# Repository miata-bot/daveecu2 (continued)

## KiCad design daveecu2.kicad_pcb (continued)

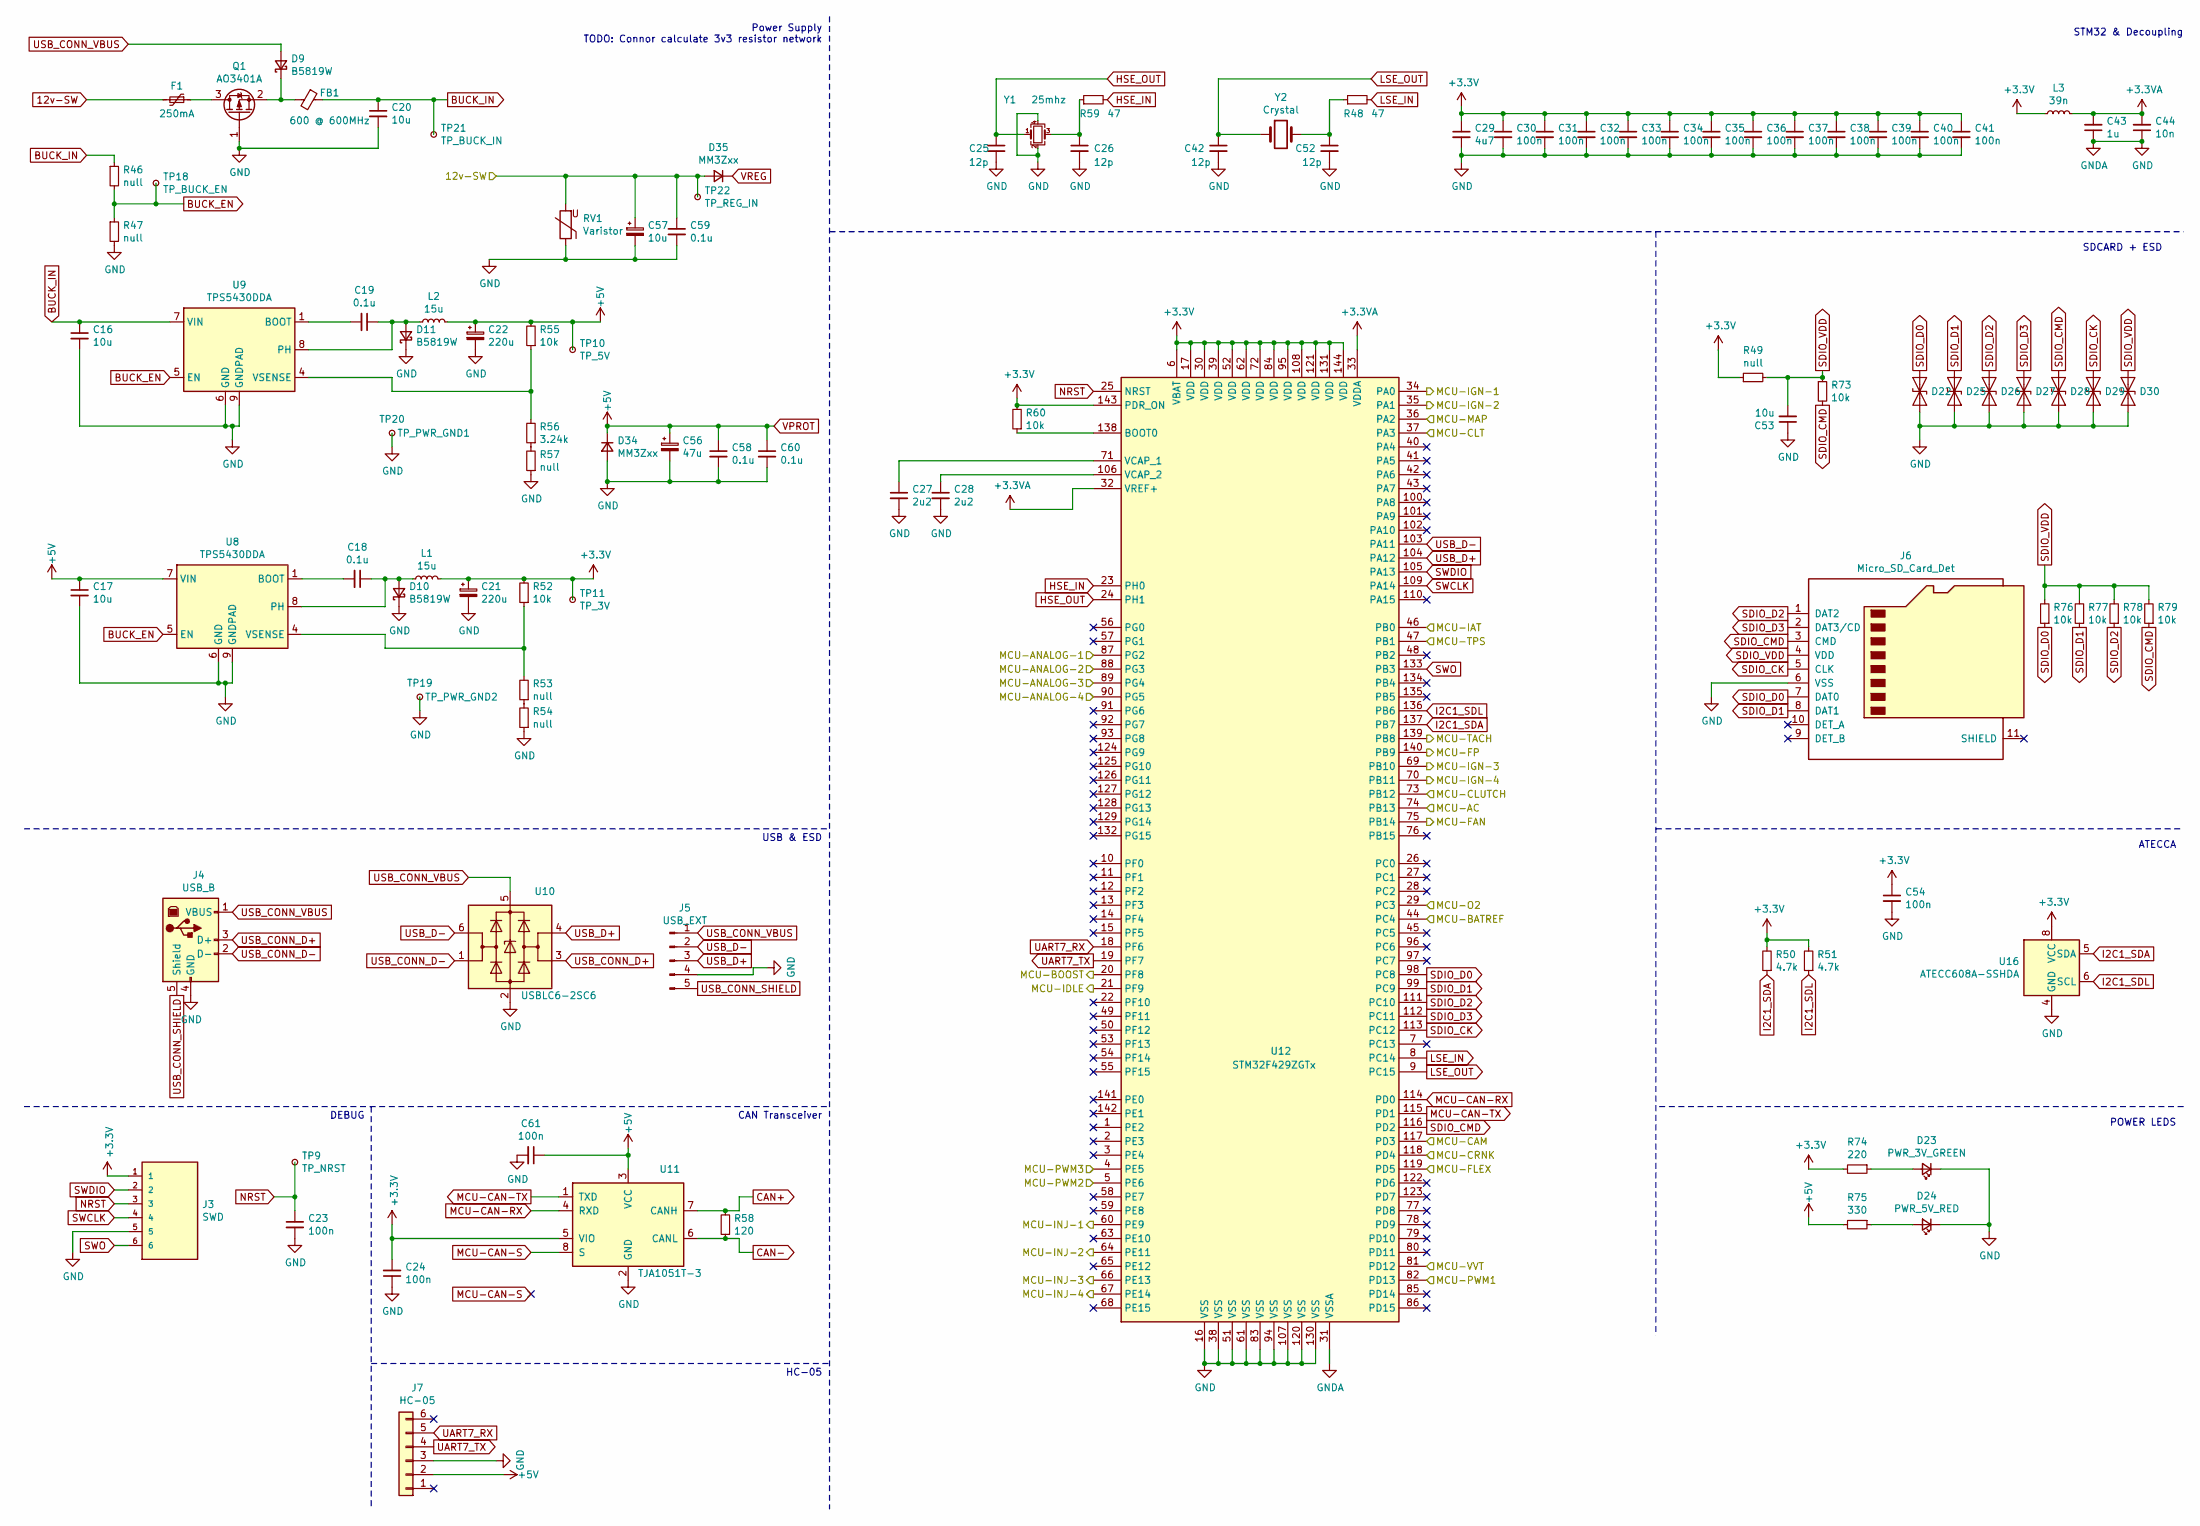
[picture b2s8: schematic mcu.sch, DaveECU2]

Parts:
C16, C17: 10u; C_1206_3216Metric_Pad1.33x1.80mm_HandSolder
C18, C19: 0.1u; C_0603_1608Metric_Pad1.08x0.95mm_HandSolder
C20: 10u; C_0603_1608Metric_Pad1.08x0.95mm_HandSolder
C21, C22: 220u; CP_Elec_10x14.3; LCSC_PN C401904
C23, C24, C30, C31, C32, C33, C34, C35, C36, C37, C38, C39, C40, C41, C54, C61: 100n; C_0402_1005Metric_Pad0.74x0.62mm_HandSolder
C25, C26, C42, C52: 12p; C_0402_1005Metric_Pad0.74x0.62mm_HandSolder
C27, C28: 2u2; C_0603_1608Metric_Pad1.08x0.95mm_HandSolder
C29: 4u7; C_0603_1608Metric_Pad1.08x0.95mm_HandSolder
C43: 1u; C_0402_1005Metric_Pad0.74x0.62mm_HandSolder
C44: 10n; C_0402_1005Metric_Pad0.74x0.62mm_HandSolder
C53: 10u; C_0402_1005Metric_Pad0.74x0.62mm_HandSolder
C56: 47u; CP_Elec_5x5.8; LCSC_PN C336380
C57: 10u; CP_EIA-7343-20_Kemet-V_Pad2.25x2.55mm_HandSolder; LCSC_PN C117038
C58, C59, C60: 0.1u; C_1206_3216Metric_Pad1.33x1.80mm_HandSolder; LCSC_PN C141184
D9, D10, D11: B5819W; D_SOD-123; LCSC_PN C541627
D22, D25, D26, D27, D28, D29, D30: ESD9B3.3ST5G; D_SOD-923; LCSC_PN C96512
D23: PWR_3V_GREEN; LED_0603_1608Metric_Pad1.05x0.95mm_HandSolder; LCSC_PN C440518
D24: PWR_5V_RED; LED_0603_1608Metric_Pad1.05x0.95mm_HandSolder; LCSC_PN C192315
D34, D35: MM3Zxx; D_SOD-323_HandSoldering; LCSC_PN C152524
F1: 250mA; Fuse_1206_3216Metric_Pad1.42x1.75mm_HandSolder
FB1: 600 @ 600MHz; L_0805_2012Metric_Pad1.05x1.20mm_HandSolder
J3: SWD; TAG_TC2030-IDC-NL; PARTREV MS
J4: USB_B; USB_B_Lumberg_2411_02_Horizontal
J5: USB_EXT; PinHeader_1x05_P2.54mm_Vertical_SMD_Pin1Left
J6: Micro_SD_Card_Det; microSD_HC_Molex_104031-0811
J7: HC-05; PinHeader_1x06_P2.54mm_Vertical
L1, L2: 15u; L_Sunlord_MWSA0518_5.4x5.2mm; LCSC_PN C139506
L3: 39n; L_0402_1005Metric_Pad0.77x0.64mm_HandSolder
Q1: AO3401A; SOT-23
R46, R47, R49, R53, R54, R57: null; R_0603_1608Metric_Pad0.98x0.95mm_HandSolder
R48, R59: 47; R_0402_1005Metric_Pad0.72x0.64mm_HandSolder
R50, R51: 4.7k; R_0603_1608Metric_Pad0.98x0.95mm_HandSolder
R52, R55, R73, R76, R77, R78, R79: 10k; R_0603_1608Metric_Pad0.98x0.95mm_HandSolder
R56: 3.24k; R_0603_1608Metric_Pad0.98x0.95mm_HandSolder
R58: 120; R_0603_1608Metric_Pad0.98x0.95mm_HandSolder
R60: 10k; R_0402_1005Metric_Pad0.72x0.64mm_HandSolder
R74: 220; R_0603_1608Metric_Pad0.98x0.95mm_HandSolder
R75: 330; R_0603_1608Metric_Pad0.98x0.95mm_HandSolder
RV1: Varistor; RV_Disc_D15.5mm_W3.9mm_P7.5mm; LCSC_PN C1527916
TP9: TP_NRST; TestPoint_Pad_D1.0mm
TP10: TP_5V; TestPoint_Pad_D1.0mm
TP11: TP_3V; TestPoint_Pad_D1.0mm
TP18: TP_BUCK_EN; TestPoint_Pad_D1.0mm
TP19: TP_PWR_GND2; TestPoint_Pad_D1.0mm
TP20: TP_PWR_GND1; TestPoint_Pad_D1.0mm
TP21: TP_BUCK_IN; TestPoint_Pad_D1.0mm
TP22: TP_REG_IN; TestPoint_Pad_D1.0mm
U8, U9: TPS5430DDA; TI_SO-PowerPAD-8_ThermalVias
U10: USBLC6-2SC6; SOT-23-6
U11: TJA1051T-3; SOIC-8_3.9x4.9mm_P1.27mm
U12: STM32F429ZGTx; LQFP-144_20x20mm_P0.5mm
U16: ATECC608A-SSHDA; SOIC-8_3.9x4.9mm_P1.27mm; LCSC_PN C2650407
Y1: 25mhz; Crystal_SMD_3225-4Pin_3.2x2.5mm_HandSoldering; LCSC_PN C439049
Y2: Crystal; Crystal_SMD_3215-2Pin_3.2x1.5mm; LCSC_PN C97604

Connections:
12v-SW: C57.1, C59.1, D35.2 (A), F1.2, RV1.2, TP22.1; also elsewhere on the board
+3.3VA: C43.2, C44.2, L3.2, U12.32 (VREF+), U12.33 (VDDA)
+3V3: C21.1, C24.2, C29.1, C30.1, C31.1, C32.1, C33.1, C34.1, C35.1, C36.1, C37.1, C38.1, C39.1, C40.1, C41.1, C54.1, J3.1, L1.2, L3.1, R49.1, R50.2, R51.2, R52.2, R60.2, R74.2, TP11.1, U11.5 (VIO), U12.6 (VBAT), U12.17 (VDD), U12.30 (VDD), U12.39 (VDD), U12.52 (VDD), U12.62 (VDD), U12.72 (VDD), U12.84 (VDD), U12.95 (VDD), U12.108 (VDD), U12.121 (VDD), U12.131 (VDD), U12.143 (PDR_ON), U12.144 (VDD), U16.8 (VCC)
/FAN+TACH/MCU-FAN: U12.75 (PB14); also elsewhere on the board
/FAN+TACH/MCU-FP: U12.140 (PB9); also elsewhere on the board
/FAN+TACH/MCU-TACH: U12.139 (PB8); also elsewhere on the board
/IDLE+BOOST/MCU-BOOST: U12.20 (PF8); also elsewhere on the board
/IDLE+BOOST/MCU-IDLE: U12.21 (PF9); also elsewhere on the board
/Ignitors/MCU-IGN-1: U12.34 (PA0); also elsewhere on the board
/Ignitors/MCU-IGN-2: U12.35 (PA1); also elsewhere on the board
/Ignitors/MCU-IGN-3: U12.69 (PB10); also elsewhere on the board
/Ignitors/MCU-IGN-4: U12.70 (PB11); also elsewhere on the board
/Injectors/MCU-INJ-1: U12.60 (PE9); also elsewhere on the board
/Injectors/MCU-INJ-2: U12.64 (PE11); also elsewhere on the board
/Injectors/MCU-INJ-3: U12.66 (PE13); also elsewhere on the board
/Injectors/MCU-INJ-4: U12.67 (PE14); also elsewhere on the board
/Sensors/MCU-AC: U12.74 (PB13); also elsewhere on the board
/Sensors/MCU-CLUTCH: U12.73 (PB12); also elsewhere on the board
/mcu/MCU-PWM1: U12.82 (PD13); also elsewhere on the board
/mcu/MCU-PWM2: U12.5 (PE6); also elsewhere on the board
/mcu/MCU-PWM3: U12.4 (PE5); also elsewhere on the board
/mcu/MCU-VVT: U12.81 (PD12); also elsewhere on the board
ADC-CLAMP-1: U12.87 (PG2); also elsewhere on the board
ADC-CLAMP-2: U12.88 (PG3); also elsewhere on the board
ADC-CLAMP-3: U12.89 (PG4); also elsewhere on the board
ADC-CLAMP-4: U12.90 (PG5); also elsewhere on the board
ADC-CLAMP-5: U12.118 (PD4); also elsewhere on the board
ADC-CLAMP-6: U12.117 (PD3); also elsewhere on the board
ADC-CLAMP-7: U12.119 (PD5); also elsewhere on the board
ADC-CLAMP-9: U12.36 (PA2); also elsewhere on the board
ADC-CLAMP-10: U12.37 (PA3); also elsewhere on the board
ADC-CLAMP-11: U12.29 (PC3); also elsewhere on the board
ADC-CLAMP-12: U12.44 (PC4); also elsewhere on the board
ADC-CLAMP-13: U12.46 (PB0); also elsewhere on the board
ADC-CLAMP-14: U12.47 (PB1); also elsewhere on the board
BUCK_EN: R46.2, R47.1, TP18.1, U8.5 (EN), U9.5 (EN)
BUCK_IN: C16.1, C20.1, FB1.1, R46.1, TP21.1, U9.7 (VIN)
CAN+: R58.2, U11.7 (CANH); also elsewhere on the board
CAN-: R58.1, U11.6 (CANL); also elsewhere on the board
GND: C16.2, C17.2, C20.2, C21.2, C22.2, C23.2, C24.1, C25.2, C26.2, C27.2, C28.2, C29.2, C30.2, C31.2, C32.2, C33.2, C34.2, C35.2, C36.2, C37.2, C38.2, C39.2, C40.2, C41.2, C42.2, C43.1, C44.1, C52.2, C53.1, C54.2, C56.2, C57.2, C58.2, C59.2, C60.2, C61.2, D10.1 (K), D11.1 (K), D22.2 (A2), D23.1 (K), D24.1 (K), D25.2 (A2), D26.2 (A2), D27.2 (A2), D28.2 (A2), D29.2 (A2), D30.2 (A2), D34.2 (A), J3.5, J4.4 (GND), J5.4, J6.6 (VSS), J7.3, Q1.1 (G), R47.2, R54.1, R57.1, RV1.1, TP19.1, TP20.1, U8.6 (GND), U8.9 (GNDPAD), U9.6 (GND), U9.9 (GNDPAD), U10.2 (GND), U11.2 (GND), U12.16 (VSS), U12.31 (VSSA), U12.38 (VSS), U12.51 (VSS), U12.61 (VSS), U12.83 (VSS), U12.94 (VSS), U12.107 (VSS), U12.120 (VSS), U12.130 (VSS), U16.4 (GND), Y1.2, Y1.4; also elsewhere on the board
HSE_IN: R59.2, U12.23 (PH0)
HSE_OUT: C25.1, U12.24 (PH1), Y1.1
I2C1_SDA: R50.1, U12.137 (PB7), U16.5 (SDA)
I2C1_SDL: R51.1, U12.136 (PB6), U16.6 (SCL)
LSE_IN: R48.2, U12.8 (PC14)
LSE_OUT: C42.1, U12.9 (PC15), Y2.1
MCU-CAN-RX: U11.4 (RXD), U12.114 (PD0)
MCU-CAN-TX: U11.1 (TXD), U12.115 (PD1)
NRST: C23.1, J3.3, TP9.1, U12.25 (NRST)
unnamed: C18.1, D10.2 (A), L1.1, U8.8 (PH)
unnamed: C18.2, U8.1 (BOOT)
unnamed: C19.1, D11.2 (A), L2.1, U9.8 (PH)
unnamed: C19.2, U9.1 (BOOT)
unnamed: C26.1, R59.1, Y1.3
unnamed: C27.1, U12.71 (VCAP_1)
unnamed: C28.1, U12.106 (VCAP_2)
unnamed: C52.1, R48.1, Y2.2
unnamed: D9.1 (K), FB1.2, Q1.2 (S)
unnamed: D23.2 (A), R74.1
unnamed: D24.2 (A), R75.1
unnamed: F1.1, Q1.3 (D)
unnamed: R52.1, R53.2, U8.4 (VSENSE)
unnamed: R53.1, R54.2
unnamed: R55.1, R56.2, U9.4 (VSENSE)
unnamed: R56.1, R57.2
unnamed: R60.1, U12.138 (BOOT0)
SDIO_CK: D29.1 (A1), J6.5 (CLK), U12.113 (PC12)
SDIO_CMD: D28.1 (A1), J6.3 (CMD), R73.2, R79.1, U12.116 (PD2)
SDIO_D0: D22.1 (A1), J6.7 (DAT0), R76.1, U12.98 (PC8)
SDIO_D1: D25.1 (A1), J6.8 (DAT1), R77.1, U12.99 (PC9)
SDIO_D2: D26.1 (A1), J6.1 (DAT2), R78.1, U12.111 (PC10)
SDIO_D3: D27.1 (A1), J6.2 (DAT3/CD), U12.112 (PC11)
SDIO_VDD: C53.2, D30.1 (A1), J6.4 (VDD), R49.2, R73.1, R76.2, R77.2, R78.2, R79.2
SWCLK: J3.4, U12.109 (PA14)
SWDIO: J3.2, U12.105 (PA13)
SWO: J3.6, U12.133 (PB3)
UART7_RX: J7.5, U12.18 (PF6)
UART7_TX: J7.4, U12.19 (PF7)
USB_CONN_D+: J4.3 (D+), U10.3 (I/O2)
USB_CONN_D-: J4.2 (D-), U10.1 (I/O1)
USB_CONN_SHIELD: J4.5 (Shield), J5.5
USB_CONN_VBUS: D9.2 (A), J4.1 (VBUS), J5.1, U10.5 (VBUS)
USB_D+: J5.3, U10.4 (I/O2), U12.104 (PA12)
USB_D-: J5.2, U10.6 (I/O1), U12.103 (PA11)
VPROT: C17.1, C22.1, C56.1, C58.1, C60.1, C61.1, D34.1 (K), J7.2, L2.2, R55.2, R75.2, TP10.1, U8.7 (VIN), U11.3 (VCC); also elsewhere on the board
VREG: D35.1 (K); also elsewhere on the board

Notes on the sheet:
Power Supply TODO: Connor calculate 3v3 resistor network
USB & ESD
DEBUG
STM32 & Decoupling
CAN Transceiver
SDCARD + ESD
ATECCA
POWER LEDS
HC-05

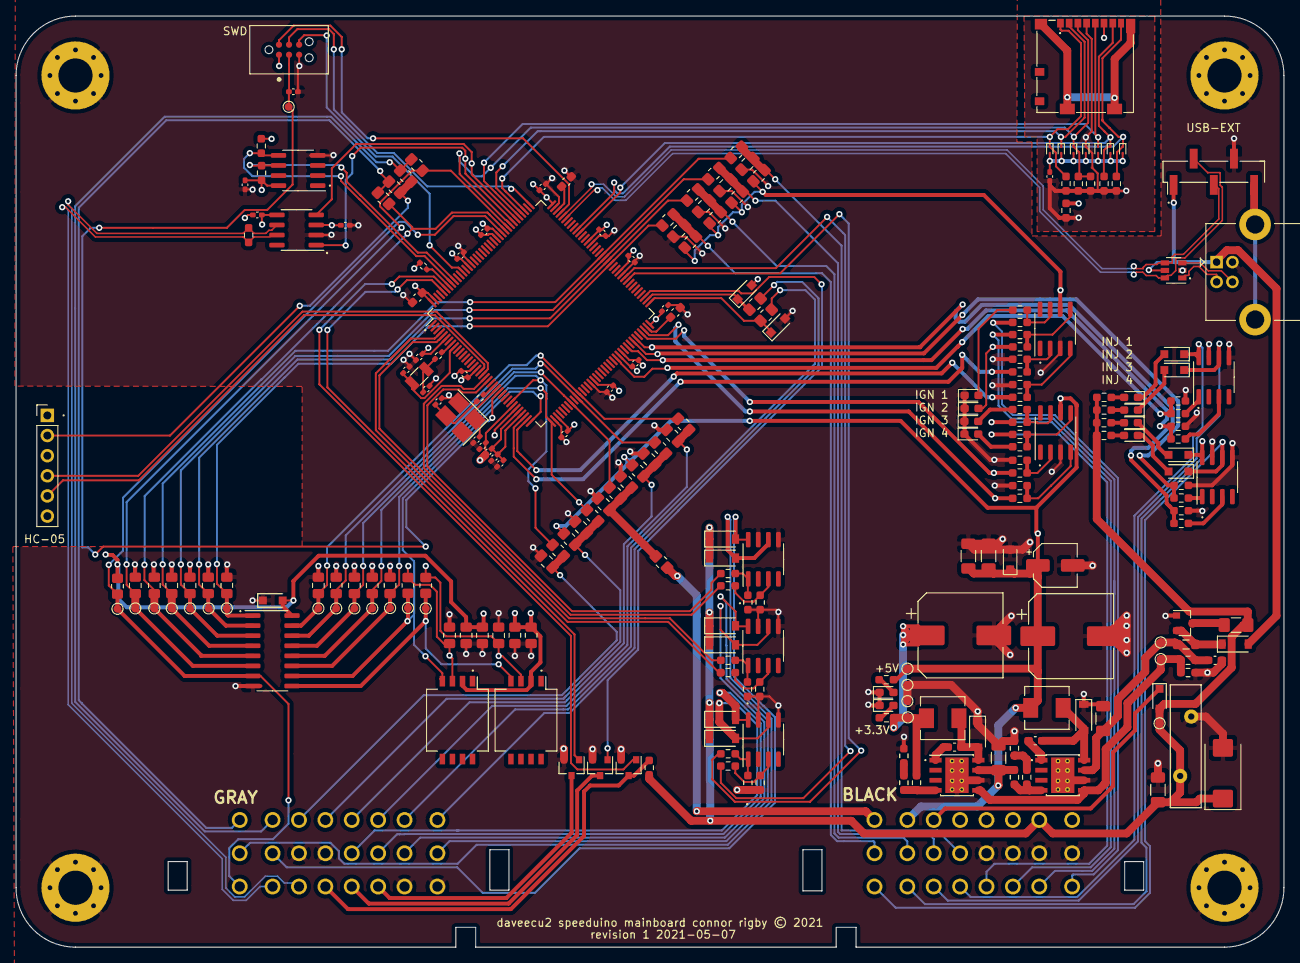
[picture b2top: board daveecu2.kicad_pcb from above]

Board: 4 copper layers, 160.0 x 117.5 mm, 249 parts (0 on the bottom side), 150 nets.

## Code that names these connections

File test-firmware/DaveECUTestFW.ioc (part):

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PB13.GPIOParameters=GPIO_Label
PD12.GPIO_Label=VVT
PE11.GPIOParameters=GPIO_Label
PG4.Signal=GPIO_Analog
PC12.Signal=SDIO_CK
PB14.GPIO_Label=FAN
PD3.GPIOParameters=GPIO_Label
PA3.GPIOParameters=GPIO_Label
PB13.Signal=GPIO_Input
PA2.GPIOParameters=GPIO_Label
RCC.SYSCLKSource=RCC_SYSCLKSOURCE_HSE
PA4.Mode=NSS_Signal_Hard_Input
PF7.Signal=UART7_TX
PD4.Signal=GPXTI4
PB6.Signal=I2C1_SCL
PH1/OSC_OUT.Signal=RCC_OSC_OUT
PB6.Mode=I2C
PC3.Signal=GPIO_Analog
PD0.Signal=CAN1_RX
PE5.Signal=S_TIM9_CH1
PB3.Mode=Trace_Asynchronous_SW
PB12.GPIO_Label=LAUNCH
PB0.GPIOParameters=GPIO_Label
PA1.GPIOParameters=GPIO_Label
PC4.GPIO_Label=BAT
PE9.Signal=S_TIM1_CH1
PB1.GPIO_Label=TPS
PC9.Mode=SD_4_bits_Wide_bus
PA8.Signal=GPIO_Output
PB14.Stacked=true
Mcu.Package=LQFP144
PB9.Signal=S_TIM4_CH4
PB1.Signal=ADCx_IN9
PF8.GPIOParameters=GPIO_Label
PD12.Signal=S_TIM4_CH1
PD5.GPIOParameters=GPIO_Label
PA10.Signal=GPIO_Output
PC11.Mode=SD_4_bits_Wide_bus
PB14.GPIOParameters=GPIO_Label
PB10.GPIOParameters=GPIO_Label
PC4.GPIOParameters=GPIO_Label
PA5.Mode=Full_Duplex_Master
PA0/WKUP.GPIOParameters=GPIO_Label
PG5.Signal=GPIO_Analog
PA9.GPIO_Label=RN1
PD3.Signal=GPXTI3
PB11.GPIO_Label=IGN4
PD1.Signal=CAN1_TX
PF8.GPIO_Label=BOOST
PC3.GPIOParameters=GPIO_Label
PB8.GPIO_Label=TACH
PA8.GPIO_Label=CEL
PA9.Signal=GPIO_Output
PB11.GPIOParameters=GPIO_Label
PE9.GPIO_Label=INJ1
PB10.Signal=S_TIM2_CH3
PB14.Signal=SharedStack_PB14
PA5.Signal=SPI1_SCK
PE13.GPIOParameters=GPIO_Label
PC12.Mode=SD_4_bits_Wide_bus
PD1.Mode=CAN_Activate
PE14.Signal=S_TIM1_CH4
PB15.GPIO_Label=VVT
PA1.GPIO_Label=IGN2
PA0/WKUP.GPIO_Label=IGN1
PA13.Mode=Trace_Asynchronous_SW
PF9.GPIOParameters=GPIO_Label
PC8.Mode=SD_4_bits_Wide_bus
PA4.Signal=SPI1_NSS
PE13.GPIO_Label=INJ3
PA11.Signal=USB_OTG_FS_DM
PF6.Mode=Asynchronous
PF9.Signal=S_TIM14_CH1
PC3.GPIO_Label=O2
PC15/OSC32_OUT.Signal=RCC_OSC32_OUT
PD2.Signal=SDIO_CMD
PB0.Signal=ADCx_IN8
PB12.GPIOParameters=GPIO_Label
PA6.Mode=Full_Duplex_Master
Mcu.UserName=STM32F429ZGTx
PG2.Signal=GPIO_Analog
PE11.GPIO_Label=INJ2
PC10.Signal=SDIO_D2
PA9.GPIOParameters=GPIO_Label
PA11.Mode=Device_Only
PA0/WKUP.Signal=S_TIM2_CH1_ETR
PC14/OSC32_IN.Mode=LSE-External-Oscillator
PB0.GPIO_Label=IAT
PB13.GPIO_Label=AC
PB11.Signal=S_TIM2_CH4
PB15.Signal=S_TIM12_CH2
PD13.Signal=S_TIM4_CH2
PA12.Signal=USB_OTG_FS_DP
PH0/OSC_IN.Mode=HSE-External-Oscillator
PA8.GPIOParameters=GPIO_Label
RCC.HSE_VALUE=25000000
PE13.Signal=S_TIM1_CH3
PA14.Mode=Trace_Asynchronous_SW
PA10.GPIO_Label=RN2
PB7.Signal=I2C1_SDA
PH1/OSC_OUT.Mode=HSE-External-Oscillator
PA6.Signal=SPI1_MISO
PC14/OSC32_IN.Signal=RCC_OSC32_IN
PD5.GPIO_Label=FLEX
PA2.GPIO_Label=MAP
PF8.Signal=S_TIM13_CH1
PC5.Signal=GPIO_Analog
PD3.GPIO_Label=CAM
PA3.Signal=GPIO_Analog
PB8.GPIOParameters=GPIO_Label
PA7.Mode=Full_Duplex_Master
PE14.GPIOParameters=GPIO_Label
PB9.GPIO_Label=FUELPUMP
PG3.Signal=GPIO_Analog
PC11.Signal=SDIO_D3
PC8.Signal=SDIO_D0
PC4.Signal=GPIO_Analog
PC10.Mode=SD_4_bits_Wide_bus
PE14.GPIO_Label=INJ4
PD5.Signal=GPXTI5
PE9.GPIOParameters=GPIO_Label
PB9.GPIOParameters=GPIO_Label
PA13.Signal=SYS_JTMS-SWDIO
PF7.Mode=Asynchronous
PF6.Signal=UART7_RX
PD12.GPIOParameters=GPIO_Label
PB10.GPIO_Label=IGN3
PC5.GPIOParameters=GPIO_Label
PF9.GPIO_Label=IDLE
PE11.Signal=S_TIM1_CH2
PA1.Signal=S_TIM2_CH2
PD2.Mode=SD_4_bits_Wide_bus
board=custom
PH0/OSC_IN.Signal=RCC_OSC_IN
PD4.GPIO_Label=CRANK
PA10.GPIOParameters=GPIO_Label
PD4.GPIOParameters=GPIO_Label
PE6.Signal=S_TIM9_CH2
PB15.GPIOParameters=GPIO_Label
Mcu.Name=STM32F429Z(E-G)Tx
PD0.Mode=CAN_Activate
PA2.Signal=GPIO_Analog
PB3.Signal=SYS_JTDO-SWO
RCC.SYSCLKFreq_VALUE=25000000
PA12.Mode=Device_Only
PC5.GPIO_Label=BARO
PC15/OSC32_OUT.Mode=LSE-External-Oscillator
PB7.Mode=I2C
PA14.Signal=SYS_JTCK-SWCLK
PB8.Signal=S_TIM4_CH3
PC9.Signal=SDIO_D1
PB12.Signal=GPIO_Input
PA3.GPIO_Label=CLT
PB1.GPIOParameters=GPIO_Label
PA7.Signal=SPI1_MOSI

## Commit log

2020-06-18 Almost finished w/ schematic
2020-06-21 Starting on layout
2021-04-21 restart a third time
2021-04-22 Layout p much finished.. Time for some stretch goals..?
2021-04-22 Upodate README and screenshot
2021-04-22 Misc Cleanup
2021-04-22 rename project
2021-04-22 Update Schematic with a bunch of extra stuff
2021-04-23 Start rerouting again
2021-04-23 Hello Miata Discord
2021-04-23 Layout checkpoint: everything fits on the board
2021-04-25 Finish reroute again
2021-04-27 Swapped the LEDs, added resistor values
2021-04-28 Fixed LED names, added resistor values
2021-05-04 Reload netlist for new LED nets
2021-05-04 Update README.md and board image
2021-05-07 Schematic and Layout Updates
    * cleanup unused pins for DRC
    * swap swd connector for the fancy one the phill uses
    * swap out the CAN transciever for one more suitable for 3v3
    * reroute CAN differential pair
    * clean up copper pours
2021-05-07 More routing updates
    * added stitching vias
    * organized sensor sheet
    * moved the CAN and Security chips closer together to clean up fills
    * added silkscreen text to some things
2021-05-07 Changed ignition drivers, set the proper package and datasheet on them
2021-05-07 Changed ignitor names back to U?
2021-05-07 Start building PNP board for na6 miata
